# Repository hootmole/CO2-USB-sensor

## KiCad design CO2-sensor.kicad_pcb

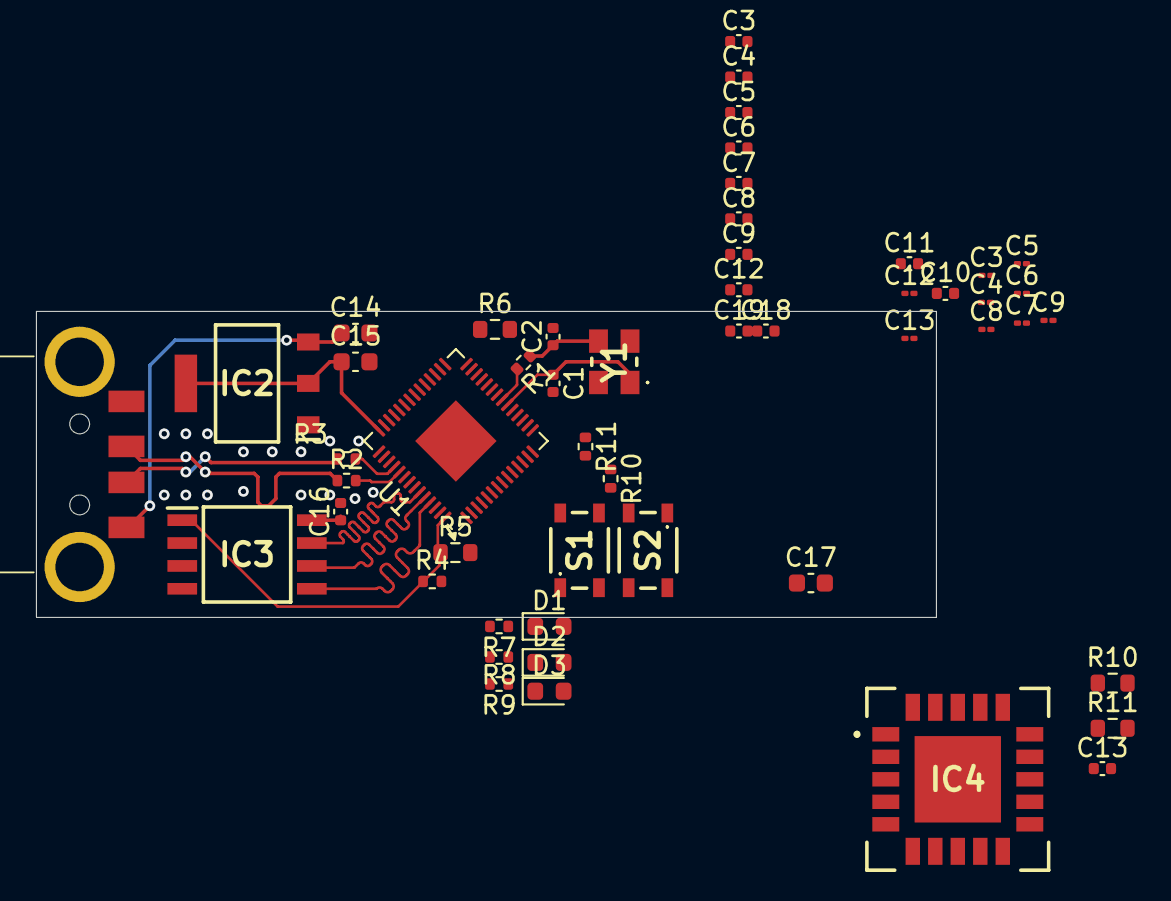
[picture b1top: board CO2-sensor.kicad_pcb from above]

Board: 2 copper layers, 50.0 x 17.0 mm, 52 parts (0 on the bottom side), 25 nets.

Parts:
C1, C2: 15p; C_0402_1005Metric
C3, C4#2, C5#2, C6#2, C7, C8#2, C9, C12#2: 100n; C_01005_0402Metric
C3#2, C4, C5, C6, C7#2, C8, C9#2, C11, C12, C16, C18, C19: 100n; C_0402_1005Metric
C10, C13#2: 1u; C_0402_1005Metric
C13: 1u; C_01005_0402Metric
C14, C15, C17: 10u; C_0603_1608Metric
D1, D2, D3: LED; LED_0603_1608Metric
IC2: NCP1117ST33T3G; SOT230P700X180-4N
IC3: W25Q32JVSSIQ; SOIC127P790X216-8N
IC4: SCD40-D-R2; SCD40DR2
J1: 1734028-1; 17340281
R1, R4: 1k; R_0402_1005Metric
R2, R3: 27.4; R_0402_1005Metric
R5, R6, R10#2, R11#2: 10k; R_0603_1608Metric
R7, R8, R9: 100; R_0402_1005Metric
R10, R11: 10k; R_0402_1005Metric
S1, S2: TS20-42-25-WT-160-SMT-TR; TS204225WT160SMTTR
U1: RP2040; QFN-56-1EP_7x7mm_P0.4mm_EP3.2x3.2mm
Y1: ABM8-272-T3; ABM8272T3

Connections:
+3.3V: C3.1, C3#2.1, C4.1, C4#2.1, C5.1, C5#2.1, C6.1, C6#2.1, C7.1, C7#2.1, C8.1, C8#2.1, C9.1, C9#2.1, C10.1, C15.1, C16.1, C17.1, C18.1, C19.1, IC2.2 (OUTPUT_1), IC2.4 (OUTPUT_2), IC3.8 (VCC), IC4.7 (VDD), IC4.19 (VDDH), R5.2, R6.2, R10.2, R10#2.1, R11.2, R11#2.1, U1.1 (IOVDD), U1.10 (IOVDD), U1.22 (IOVDD), U1.33 (IOVDD), U1.42 (IOVDD), U1.43 (ADC_AVDD), U1.44 (VREG_IN), U1.48 (USB_VDD), U1.49 (IOVDD)
+5V: C14.1, IC2.3 (INPUT), J1.1
/QSPI_SCLK: IC3.6 (CLK), U1.52 (QSPI_SCLK)
/QSPI_SD0: IC3.5 (DI_(IO0)), U1.53 (QSPI_SD0)
/QSPI_SD3: IC3.7 (~HOLD_OR_/RESET_(IO3)), U1.51 (QSPI_SD3)
/QSPI_SS: IC3.1 (~CS), R4.2, R5.1, U1.56 (QSPI_SS)
/SCL: IC4.9 (SCL), R11.1, R11#2.2, U1.28 (GPIO17)
/SDA: IC4.10 (SDA), R10.1, R10#2.2, U1.27 (GPIO16)
/Xin: C1.1, U1.20 (XIN), Y1.1 (CRYSTAL_1)
/Xout: R1.2, U1.21 (XOUT)
D+: J1.3, R2.1
D-: J1.2, R3.1
GND: C1.2, C2.2, C3.2, C3#2.2, C4.2, C4#2.2, C5.2, C5#2.2, C6.2, C6#2.2, C7.2, C7#2.2, C8.2, C8#2.2, C9.2, C9#2.2, C10.2, C11.2, C12.2, C12#2.2, C13.2, C13#2.2, C14.2, C15.2, C16.2, C17.2, C18.2, C19.2, IC2.1 (ADJUST/GROUND), IC3.4 (GND), IC4.6 (GND_1), IC4.20 (GND_2), IC4.21 (GND_3), J1.4, J1.MH1, J1.MH2, R7.2, R8.2, R9.2, S1.4 (COM_2), S2.1 (NO_1), U1.19 (TESTEN), U1.57 (GND), Y1.2 (GND_1), Y1.4 (GND_2)
unnamed: D1.2 (A), U1.16 (GPIO13)
unnamed: D1.1 (K), R7.1
unnamed: D2.2 (A), U1.17 (GPIO14)
unnamed: D2.1 (K), R8.1
unnamed: D3.2 (A), U1.18 (GPIO15)
unnamed: D3.1 (K), R9.1
unnamed: R4.1, S1.2 (NO_2)
unnamed: R6.1, S2.3 (COM_1), U1.26 (RUN)
unnamed: R3.2, U1.46 (USB_DM)
unnamed: R2.2, U1.47 (USB_DP)
unnamed: C11.1, C12.1, C12#2.1, C13.1, C13#2.1, U1.23 (DVDD), U1.45 (VREG_VOUT), U1.50 (DVDD)
unnamed: C2.1, R1.1, Y1.3 (CRYSTAL_2)

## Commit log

2025-08-30 First init
2025-08-31 removed components folder
